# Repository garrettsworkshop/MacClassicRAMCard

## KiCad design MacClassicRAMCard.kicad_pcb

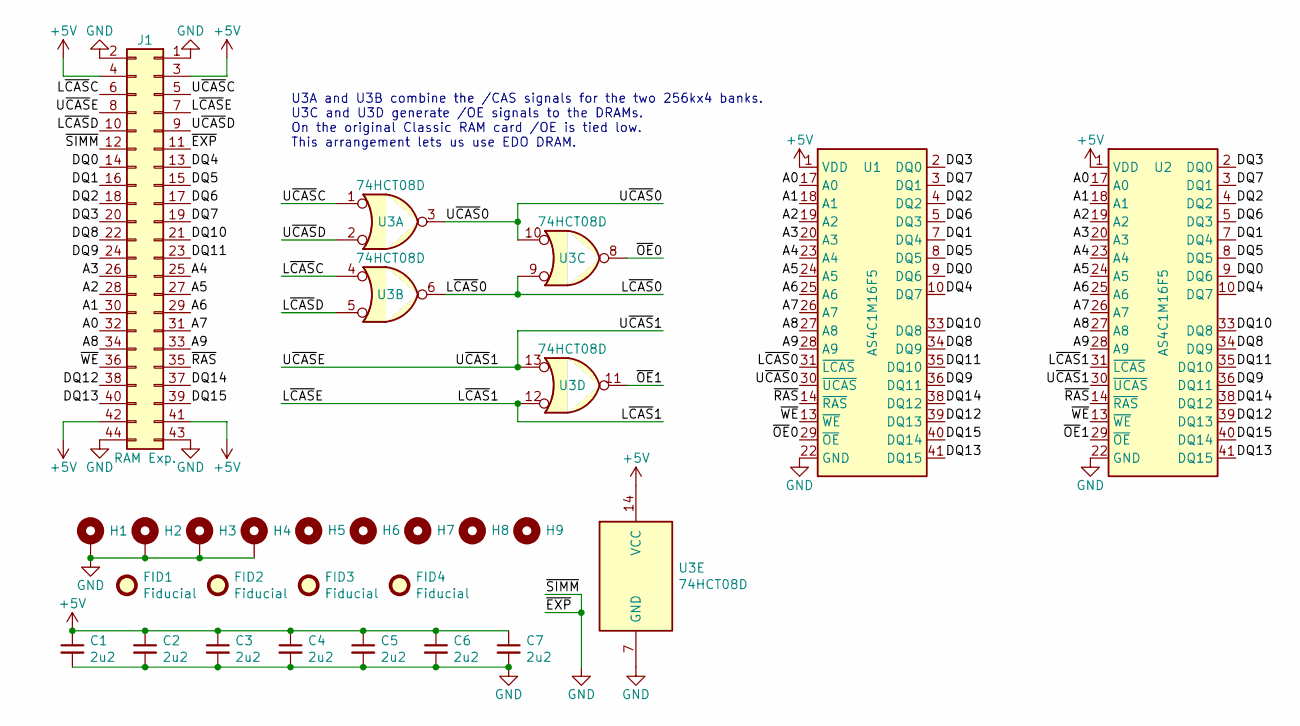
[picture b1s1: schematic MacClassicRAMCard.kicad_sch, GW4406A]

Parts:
C1, C2, C3, C4, C5, C6, C7: 2u2; C_0805
FID1, FID2, FID3, FID4: Fiducial
H1, H2, H3, H4: PasteHole_1.1mm_PTH
H5, H6, H7: PasteHole_1.152mm_NPTH
H8, H9: PasteHole_3mm_NPTH
J1: RAM Exp.; PinSocket_2x22_P2.54mm_Horizontal
U1, U2: AS4C1M16F5; SOJ-42_400mil
U3: 74HCT08D; SOIC-14_3.9mm

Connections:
+5V: C1.1, C2.1, C3.1, C4.1, C5.1, C6.1, C7.1, J1.3, J1.4, J1.41, J1.42, U1.1 (VDD), U1.6 (VDD), U1.21 (VDD), U2.1 (VDD), U2.6 (VDD), U2.21 (VDD), U3.14 (VCC)
/A0: J1.32, U1.17 (A0), U2.17 (A0)
/A1: J1.30, U1.18 (A1), U2.18 (A1)
/A2: J1.28, U1.19 (A2), U2.19 (A2)
/A3: J1.26, U1.20 (A3), U2.20 (A3)
/A4: J1.25, U1.23 (A4), U2.23 (A4)
/A5: J1.27, U1.24 (A5), U2.24 (A5)
/A6: J1.29, U1.25 (A6), U2.25 (A6)
/A7: J1.31, U1.26 (A7), U2.26 (A7)
/A8: J1.34, U1.27 (A8), U2.27 (A8)
/A9: J1.33, U1.28 (A9), U2.28 (A9)
/DQ0: J1.14, U1.9 (DQ6), U2.9 (DQ6)
/DQ1: J1.16, U1.7 (DQ4), U2.7 (DQ4)
/DQ2: J1.18, U1.4 (DQ2), U2.4 (DQ2)
/DQ3: J1.20, U1.2 (DQ0), U2.2 (DQ0)
/DQ4: J1.13, U1.10 (DQ7), U2.10 (DQ7)
/DQ5: J1.15, U1.8 (DQ5), U2.8 (DQ5)
/DQ6: J1.17, U1.5 (DQ3), U2.5 (DQ3)
/DQ7: J1.19, U1.3 (DQ1), U2.3 (DQ1)
/DQ8: J1.22, U1.34 (DQ9), U2.34 (DQ9)
/DQ9: J1.24, U1.36 (DQ11), U2.36 (DQ11)
/DQ10: J1.21, U1.33 (DQ8), U2.33 (DQ8)
/DQ11: J1.23, U1.35 (DQ10), U2.35 (DQ10)
/DQ12: J1.38, U1.39 (DQ13), U2.39 (DQ13)
/DQ13: J1.40, U1.41 (DQ15), U2.41 (DQ15)
/DQ14: J1.37, U1.38 (DQ12), U2.38 (DQ12)
/DQ15: J1.39, U1.40 (DQ14), U2.40 (DQ14)
/L~CAS0: U1.31 (~LCAS), U3.6, U3.9
/L~CAS1: J1.7, U2.31 (~LCAS), U3.12
/L~CASC: J1.6, U3.4
/L~CASD: J1.10, U3.5
/U~CAS0: U1.30 (~UCAS), U3.3, U3.10
/U~CAS1: J1.8, U2.30 (~UCAS), U3.13
/U~CASC: J1.5, U3.1
/U~CASD: J1.9, U3.2
/~OE0: U1.29 (~OE), U3.8
/~OE1: U2.29 (~OE), U3.11
/~RAS: J1.35, U1.14 (~RAS), U2.14 (~RAS)
/~WE: J1.36, U1.13 (~WE), U2.13 (~WE)
GND: C1.2, C2.2, C3.2, C4.2, C5.2, C6.2, C7.2, H1.1, H2.1, H3.1, H4.1, J1.1, J1.2, J1.11, J1.12, J1.43, J1.44, U1.22 (GND), U1.37 (GND), U1.42 (GND), U2.22 (GND), U2.37 (GND), U2.42 (GND), U3.7 (GND)

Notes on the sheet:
U3A and U3B combine the /CAS signals for the two 256kx4 banks. U3C and U3D generate /OE signals to the DRAMs. On the original Classic RAM card /OE is tied low. This arrangement lets us use EDO DRAM.

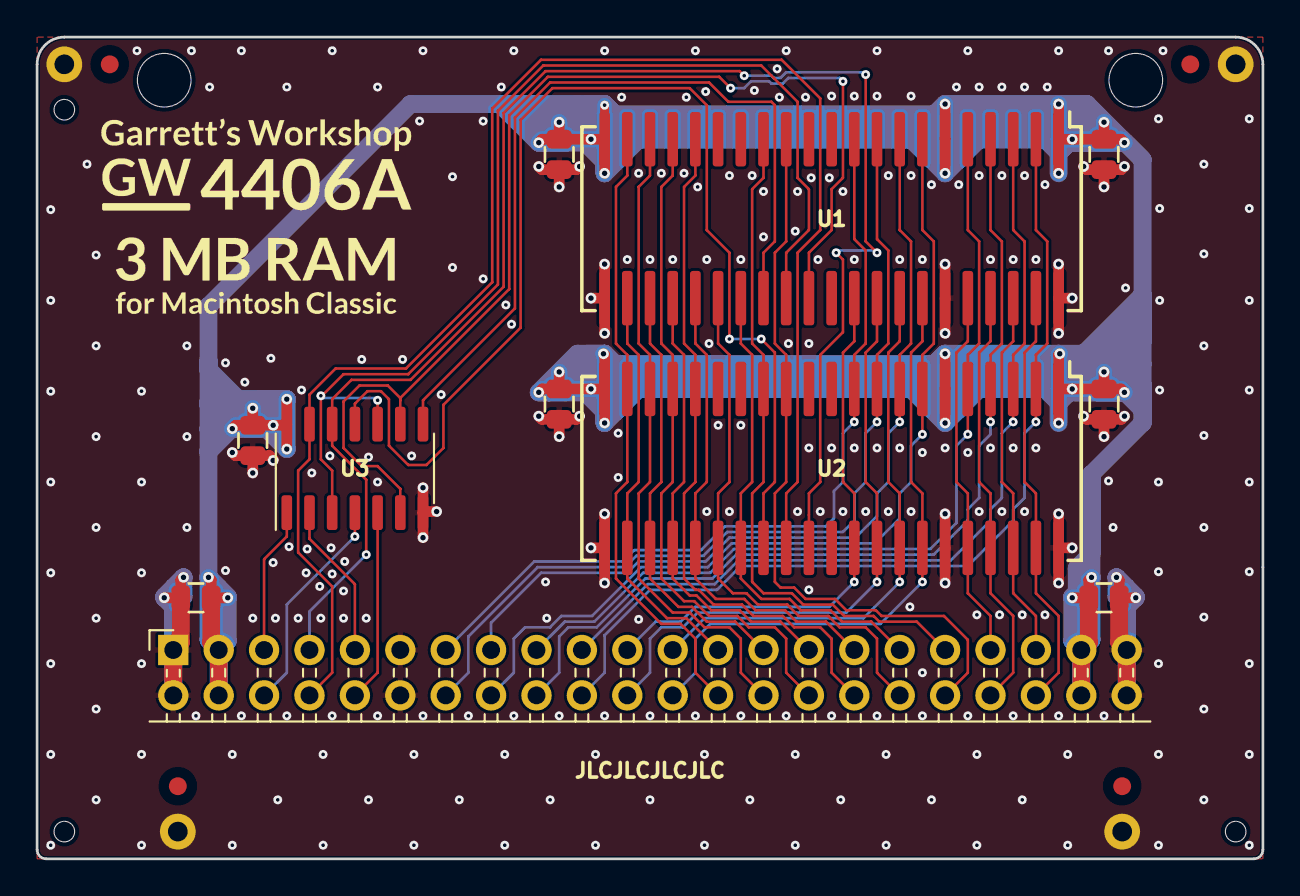
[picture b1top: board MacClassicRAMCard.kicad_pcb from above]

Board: 2 copper layers, 68.6 x 46.0 mm, 24 parts (0 on the bottom side), 40 nets.

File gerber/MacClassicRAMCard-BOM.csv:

"Ref","Qnty","Value","Cmp name","Footprint","Description","Vendor","LCSC Part"
"C1, C2, C3, C4, C5, C6, C7, ","7","2u2","C_Small","stdpads:C_0805","Unpolarized capacitor, small symbol","",""
"FID1, FID2, FID3, FID4, ","4","Fiducial","Fiducial","stdpads:Fiducial","Fiducial Marker","",""
"H1, H2, H3, H4, ","4","","MountingHole_Pad","stdpads:PasteHole_1.1mm_PTH","Mounting Hole with connection","",""
"H5, H6, H7, ","3","","MountingHole_Pad","stdpads:PasteHole_1.152mm_NPTH","Mounting Hole with connection","",""
"J1, ","1","RAM Exp.","Conn_02x22_Odd_Even","stdpads:PinSocket_2x22_P2.54mm_Horizontal","Generic connector, double row, 02x22, odd/even pin numbering scheme (row 1 odd numbers, row 2 even numbers), script generated (kicad-library-utils/schlib/autogen/connector/)","",""
"U1, U2, ","2","AS4C1M16F5","DRAM-1Mx16-SOP-42","stdpads:SOJ-42_400mil","","",""
"U3, ","1","74HCT08D","74LS08","stdpads:SOIC-14_3.9mm","Quad And2","",""

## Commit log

2021-06-20 Mostly done with layout
2021-10-29 Finished layout I think
2021-11-17 As sent to JLC
2021-11-19 No actually
2022-02-06 Migrate to KiCAD 6
2022-02-06 Switch to KiCAD 6 3d models
2022-02-11 New prototype
2022-08-10 New logo
2022-09-06 Documentation update
